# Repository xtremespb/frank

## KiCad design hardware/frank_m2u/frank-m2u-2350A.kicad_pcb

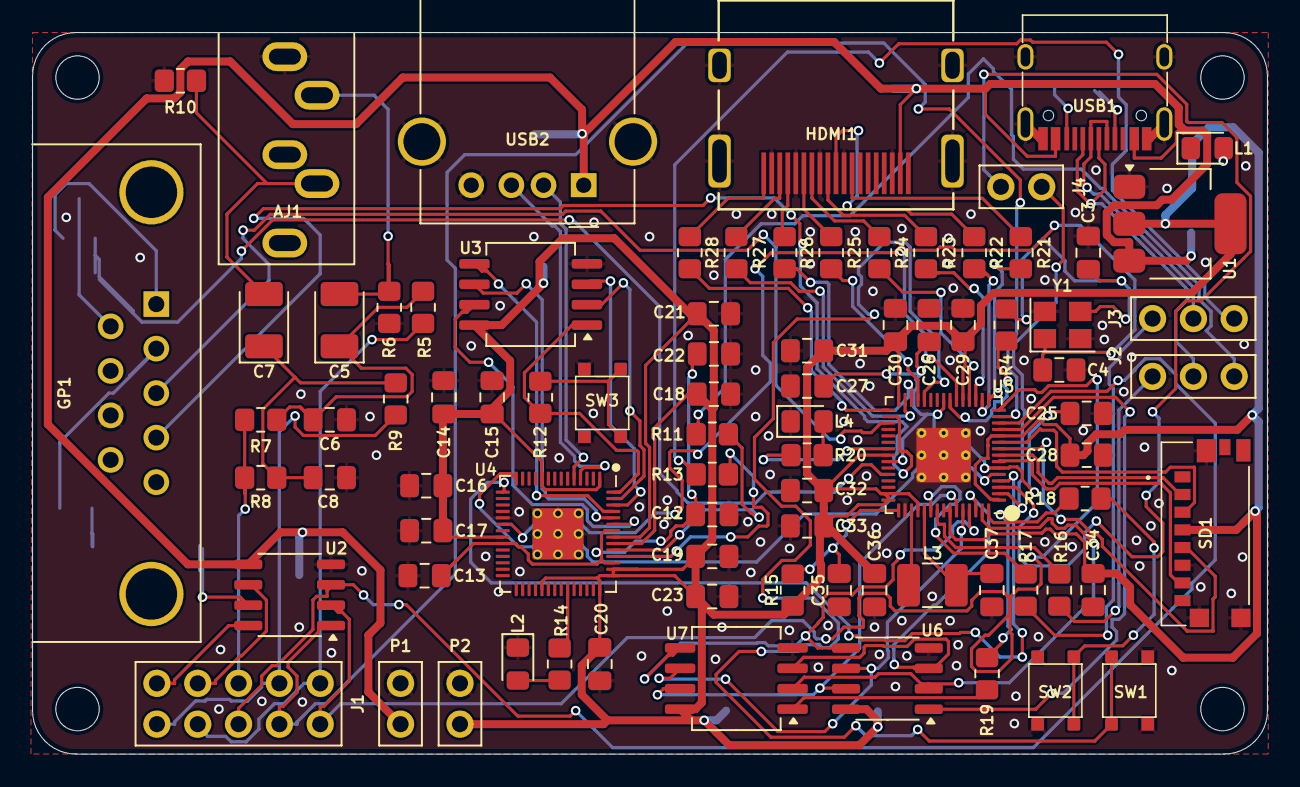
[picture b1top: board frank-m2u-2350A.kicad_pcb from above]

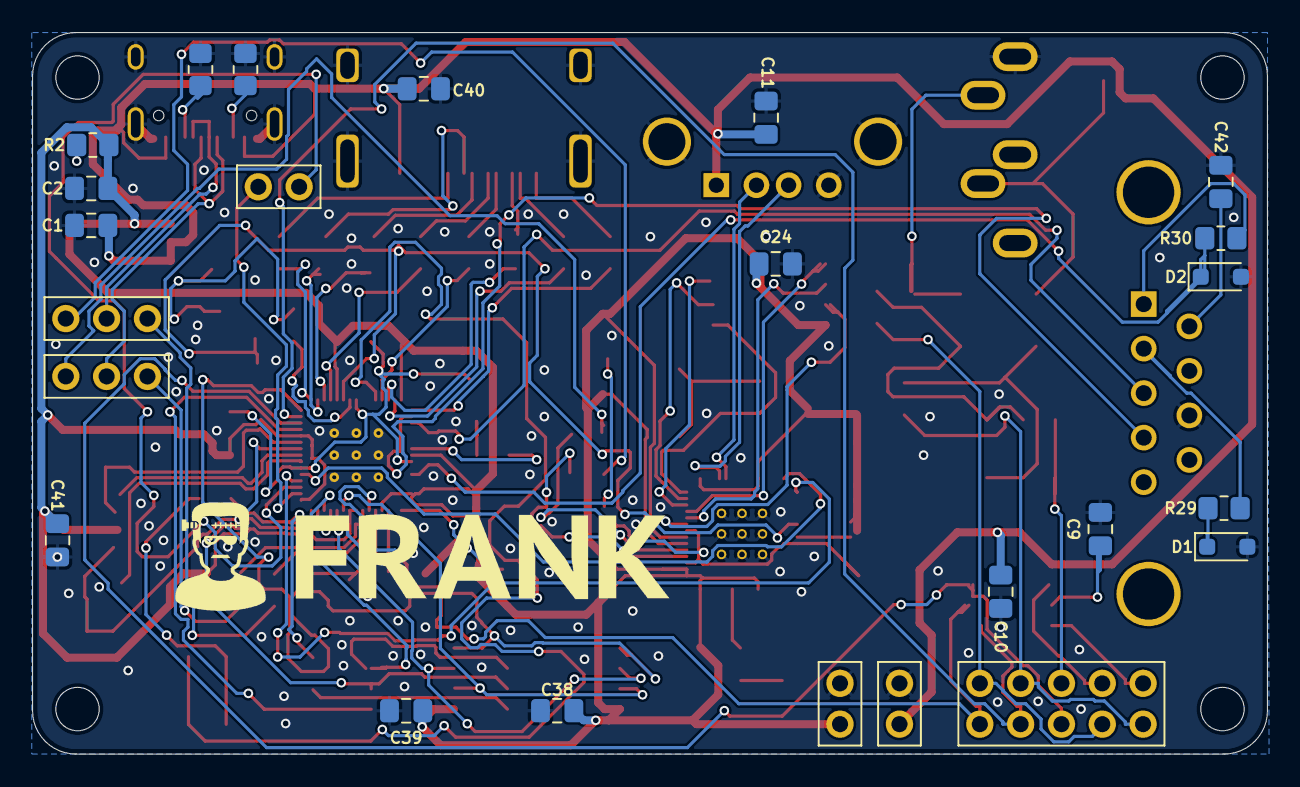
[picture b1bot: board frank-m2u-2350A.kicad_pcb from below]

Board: 2 copper layers, 76.8 x 44.9 mm, 105 parts (18 on the bottom side), 91 nets.

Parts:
AJ1: SJ1-353XNG; Jack (3.5mm)
C1, C2, C11: 10u; Capacitor (0805)
C3, C4: 15p; Capacitor (0805)
C5, C7: 10u; Capacitor (3528, tantalum, polar)
C6, C8: 10n; Capacitor (0805)
C9, C22, C23: 1u; Capacitor (0805)
C10: 47u; Capacitor (0805)
C12, C13, C14, C15, C16, C17, C18, C19, C20, C21, C24, C25, C27, C28, C29, C30, C31, C32, C33, C34, C38, C39, C40, C41, C42: 100n; Capacitor (0805)
C26, C35, C36, C37: 4.7u; Capacitor (0805)
D1, D2: 3V3; Diode (SOD-323)
GP1: Gamepad; D-SUB (9 pin, male, top mount)
H1, H2, H3, H4: MountingHole; Mounting Hole (2.7mm)
HDMI1: HDMI Female; HDMI (female)
J1: Pin Header 2x05; Pin Header (2x05)
J2: USB DP Jumper; Pin Header (1x03)
J3: USB DM Jumper; Pin Header (1x03)
J4: UART; Pin Header (1x02)
L1: Green; LED (0805)
L2: BLUE; LED (0805)
L3: 3.3uH; Inductor (3225)
L4: Blue; LED (0805)
P1: Power (+5V); Pin Header (1x02)
P2: Power (+3.3V); Pin Header (1x02)
R1, R3: 5.1K; Resistor (0805)
R2, R4, R5, R9, R12, R14, R18, R20, R29, R30: 1K; Resistor (0805)
R6, R10: 330R; Resistor (0805)
R7, R8: 2K; Resistor (0805)
R11, R13, R16, R17: 27R; Resistor (0805)
R15: 33R; Resistor (0805)
R19: 0R; Resistor (0805)
R21, R22, R23, R24, R25, R26, R27, R28: 270R; Resistor (0805)
SD1: 47571-0001; MicroSD (SMD, short)
SW1: Reset; Button (SMD, 3x3mm, 1-1)
SW2, SW3: Boot; Button (SMD, 3x3mm, 1-1)
U1: NCP1117 3.3; SOT-223
U2: TDA1387T; SO-8
U3: W25Q128JVSIQ; SOIC-8
U4: RP2040; QFN 56
U5: RP2350A; QFN 60 (RP2350A)
U6: ESP-PSRAM32; SO-8
U7: W25Q128JVSQ; SOIC-8
USB1: USB4215-03-A; USB Type C
USB2: 676430910; USB Type A (single)
Y1: 12 MHz; Crystal (3225)

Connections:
+3V3: C2.1, C14.1, C15.1, C16.1, C17.1, C18.1, C19.1, C20.1, C21.1, C23.1, C24.1, C28.1, C29.1, C30.1, C31.1, C32.1, C33.1, C34.1, C36.1, C38.1, C39.1, C41.2, P2.2, R2.2, R15.1, SD1.P4 (VDD), U1.2 (VO), U3.8 (VCC), U4.1 (IOVDD), U4.10 (IOVDD), U4.22 (IOVDD), U4.33 (IOVDD), U4.42 (IOVDD), U4.43 (ADC_AVDD), U4.44 (VREG_IN), U4.48 (USB_VDD), U4.49 (IOVDD), U5.1 (IOVDD), U5.11 (IOVDD), U5.20 (IOVDD), U5.30 (IOVDD), U5.38 (IOVDD), U5.44 (ADC_AVDD), U5.45 (IOVDD), U5.49 (VREG_VIN), U5.53 (USB_OTP_VDD), U5.54 (QSPI_IOVDD), U6.8 (VCC), U7.8 (VCC)
/A_OUTB: J1.5, R7.2, R8.2
/A_OUTL: J1.1, J1.8, R5.2
/A_OUTR: J1.3, J1.10, R9.2
/A_TDAL: J1.7, U2.6 (A_LEFT)
/A_TDAR: J1.9, U2.8 (A_RIGHT)
/Audio Out/L: AJ1.T, C5.2, R6.1
/Audio Out/R: AJ1.R, C7.2, R10.1
/GPIO0: J4.1, U5.2 (GPIO0)
/GPIO1: J4.2, U5.3 (GPIO1)
/GPIO2: U4.15 (GPIO12), U5.4 (GPIO2)
/GPIO3: U4.14 (GPIO11), U5.5 (GPIO3)
/GPIO4: SD1.P7 (DAT0), U5.7 (GPIO4)
/GPIO5: SD1.P2 (CD/DAT3), U5.8 (GPIO5)
/GPIO6: SD1.P5 (CLK), U5.9 (GPIO6)
/GPIO7: SD1.P3 (CMD), U5.10 (GPIO7)
/GPIO8: U5.12 (GPIO8), U6.1 (~CE)
/GPIO9: J1.6, U2.3 (DATA), U5.13 (GPIO9)
/GPIO10: J1.4, U2.1 (SCLK), U5.14 (GPIO10)
/GPIO11: J1.2, U2.2 (LRCK), U5.15 (GPIO11)
/GPIO12: R21.2, U5.16 (GPIO12)
/GPIO13: R22.2, U5.17 (GPIO13)
/GPIO14: R23.2, U5.18 (GPIO14)
/GPIO15: R24.2, U5.19 (GPIO15)
/GPIO16: R25.2, U5.27 (GPIO16)
/GPIO17: R26.2, U5.28 (GPIO17)
/GPIO18: R27.2, U5.29 (GPIO18)
/GPIO19: R28.2, U5.31 (GPIO19)
/GPIO20: GP1.4, U5.32 (GPIO20)
/GPIO21: GP1.3, U5.33 (GPIO21)
/GPIO26: D1.1 (K), R29.1
/GPIO27: D2.1 (K), R30.1, U5.41 (GPIO27_ADC1)
/Gamepad/+5V: C42.1, GP1.6
/Gamepad/J1_DATA: GP1.2, R29.2
/Gamepad/J2_DATA: GP1.1, R30.2
/P_DM: J3.2, USB1.5 (DN2), USB1.7 (DN1)
/P_DP: J2.2, USB1.6 (DP1), USB1.8 (DP2)
/RP1_DM: J3.1, R17.1
/RP1_DP: J2.1, R16.1
/RP2_DM: J3.3, R13.1
/RP2_DP: J2.3, R11.1
/RP2040/GPIO25: R14.2, U4.37 (GPIO25)
/RP2040/QSPI_SCLK: U3.6 (CLK), U4.52 (QSPI_SCLK)
/RP2040/QSPI_SD0: U3.5 (DI(IO0)), U4.53 (QSPI_SD0)
/RP2040/QSPI_SD1: U3.2 (DO(IO1)), U4.55 (QSPI_SD1)
/RP2040/QSPI_SD2: U3.3 (IO2), U4.54 (QSPI_SD2)
/RP2040/QSPI_SD3: U3.7 (IO3), U4.51 (QSPI_SD3)
/RP2040/QSPI_SS: R12.1, U3.1 (~CS), U4.56 (QSPI_SS)
/RP2040/~USB_BOOT: R12.2, SW3.2
/RP2350A/FLASH_SS: R19.2, U7.1 (~CS)
/RP2350A/QSPI_SCLK: U5.56 (QSPI_SCLK), U6.6 (SCLK), U7.6 (CLK)
/RP2350A/QSPI_SD0: U5.57 (QSPI_SD0), U6.5 (SI/SIO), U7.5 (DI(IO0))
/RP2350A/QSPI_SD1: U5.59 (QSPI_SD1), U6.2 (SO/SIO), U7.2 (DO(IO1))
/RP2350A/QSPI_SD2: U5.58 (QSPI_SD2), U6.3 (SIO2), U7.3 (IO2)
/RP2350A/QSPI_SD3: U5.55 (QSPI_SD3), U6.7 (SIO3), U7.7 (IO3)
/RP2350A/QSPI_SS: R18.1, R19.1, U5.60 (QSPI_SS)
/RP2350A/VREG_AVDD: C35.1, R15.2, U5.46 (VREG_AVDD)
/RP2350A/VREG_LX: L3.2, U5.48 (VREG_LX)
/RP2350A/~USB_BOOT: R18.2, SW2.2
/RUN: SW1.1, U5.26 (RUN)
/US_D1M: U4.5 (GPIO3), USB2.2 (D-)
/US_D1P: U4.4 (GPIO2), USB2.3 (D+)
/XIN: C4.1, U4.20 (XIN), U5.21 (XIN), Y1.1
/XOUT: R4.1, U5.22 (XOUT)
GND: AJ1.S, C1.2, C2.2, C3.2, C4.2, C6.2, C8.2, C9.2, C10.1, C11.1, C12.2, C13.2, C14.2, C15.2, C16.2, C17.2, C18.2, C19.2, C20.2, C21.2, C22.2, C23.2, C24.2, C25.2, C26.2, C27.2, C28.2, C29.2, C30.2, C31.2, C32.2, C33.2, C34.2, C35.2, C36.2, C37.2, C38.2, C39.2, C40.2, C41.1, C42.2, D1.2 (A), D2.2 (A), GP1.8, HDMI1.2 (G_D2), HDMI1.5 (G_D1), HDMI1.8 (G_D0), HDMI1.11 (G_CLK), HDMI1.17 (G_DDC/CEC), HDMI1.20 (SHIELD1), HDMI1.21 (SHIELD2), HDMI1.22 (SHIELD3), HDMI1.23 (SHIELD4), L1.1 (K), L2.1 (K), L4.1 (K), P1.1, P2.1, R1.1, R3.1, R6.2, R10.2, SD1.G1 (GND_1), SD1.G2 (GND_2), SD1.G3 (GND_3), SD1.P6 (VSS), SW1.2, SW2.1, SW3.1, U1.1 (GND), U2.4 (AGND), U3.4 (GND), U4.19 (TESTEN), U4.57 (GND), U5.47 (VREG_PGND), U5.61 (GND), U6.4 (VSS), U7.4 (GND), USB1.1 (GND), USB1.12 (GND), USB1.13 (SHIELD), USB2.4 (GND), USB2.5 (Shield), Y1.2, Y1.4
GPIO25: R20.2, U5.37 (GPIO25)
unnamed: C3.1, R4.2, Y1.3
unnamed: C5.1, C6.1, R5.1, R7.1
unnamed: C7.1, C8.1, R8.1, R9.1
unnamed: C25.1, C26.1, C27.1, U5.6 (DVDD), U5.23 (DVDD), U5.39 (DVDD)
unnamed: HDMI1.12 (CLKN), R21.1
unnamed: HDMI1.10 (CLKP), R22.1
unnamed: HDMI1.9 (D0N), R23.1
unnamed: HDMI1.7 (D0P), R24.1
unnamed: HDMI1.6 (D1N), R25.1
unnamed: HDMI1.4 (D1P), R26.1
unnamed: HDMI1.3 (D2N), R27.1
unnamed: HDMI1.1 (D2P), R28.1
unnamed: L1.2 (A), R2.1
unnamed: L2.2 (A), R14.1
unnamed: L4.2 (A), R20.1
unnamed: C9.1, U2.7 (FLT)
unnamed: R13.2, U4.46 (USB_DM)
unnamed: R11.2, U4.47 (USB_DP)
unnamed: C12.1, C13.1, C22.1, U4.23 (DVDD), U4.45 (VREG_VOUT), U4.50 (DVDD)
unnamed: R17.2, U5.51 (USB_DM)
unnamed: R16.2, U5.52 (USB_DP)
unnamed: C37.1, L3.1, U5.50 (VREG_FB)
unnamed: R1.2, USB1.4 (CC1)
unnamed: R3.2, USB1.10 (CC2)
VBUS: C1.1, C10.2, C11.2, C40.1, HDMI1.18 (+5V), P1.2, U1.3 (VI), U2.5 (VA), USB1.2 (VBUS), USB1.11 (VBUS), USB2.1 (VBUS)

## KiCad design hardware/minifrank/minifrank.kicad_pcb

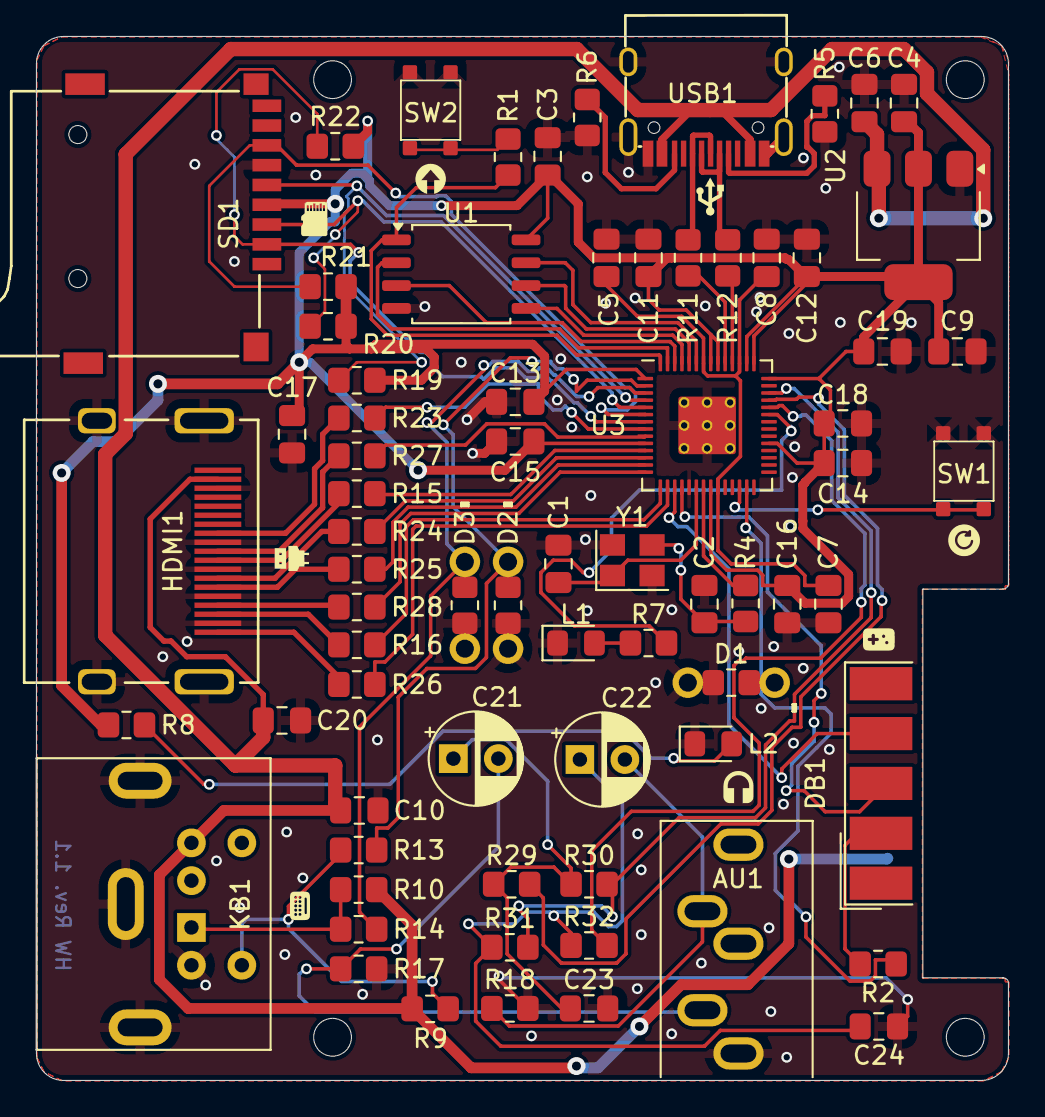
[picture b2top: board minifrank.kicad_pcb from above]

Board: 2 copper layers, 54.0 x 58.0 mm, 72 parts (0 on the bottom side), 59 nets.

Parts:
AU1: AUDIO OUT; Medved_Jack_3.5mm_CUI_SJ1-3535NG_Horizontal
C1, C2: 15p; C_0805_2012Metric_Pad1.18x1.45mm_HandSolder
C3, C5, C7, C11, C13, C14, C15, C16, C18, C19: 100n; C_0805_2012Metric_Pad1.18x1.45mm_HandSolder
C4, C6, C9: 10u; C_0805_2012Metric_Pad1.18x1.45mm_HandSolder
C8, C12: 1u; C_0805_2012Metric_Pad1.18x1.45mm_HandSolder
C10, C17, C20: 0.1u; C_0805_2012Metric_Pad1.18x1.45mm_HandSolder
C21, C22: 10u; Medved_CP_Radial_D5.0mm_P2.50mm
C23, C24: 10n; C_0805_2012Metric_Pad1.18x1.45mm_HandSolder
D1, D2, D3: 3V3; R_0805_PLUS
DB1: Joystick; DSUB-9_Male_EdgeMount_P2.77mm
HDMI1: HDMI
KB1: PS/2; Connector_Mini-DIN_Female_6Pin_2rows
L1, L2: LED; LED_0805_2012Metric_Pad1.15x1.40mm_HandSolder
R1, R2, R4, R9, R10, R29, R32: 1k; R_0805_2012Metric_Pad1.20x1.40mm_HandSolder
R5, R6: 5.1K; R_0805_2012Metric_Pad1.20x1.40mm_HandSolder
R7, R8: 1K; R_0805_2012Metric_Pad1.20x1.40mm_HandSolder
R11, R12: 27; R_0805_2012Metric_Pad1.20x1.40mm_HandSolder
R13, R14: 100R; R_0805_2012Metric_Pad1.20x1.40mm_HandSolder
R15, R16, R23, R24, R25, R26, R27, R28: 270R; R_0805_2012Metric_Pad1.20x1.40mm_HandSolder
R17, R18: 330R; R_0805_2012Metric_Pad1.20x1.40mm_HandSolder
R19, R20, R21, R22: 10K; R_0805_2012Metric_Pad1.20x1.40mm_HandSolder
R30, R31: 2k; R_0805_2012Metric_Pad1.20x1.40mm_HandSolder
SD1: Micro SD; Medved_SD_Card
SW1: Reset Button; Button_SMD_3x3x2
SW2: Flash Button; Button_SMD_3x3x2
U1: W25Q128JVS; SOIC-8_5.23x5.23mm_P1.27mm
U2: NCP1117-3.3_SOT223; Medved_SOT-223-3_TabPin2
U3: RP2040; RP2040-QFN-56
USB1: USB Type C; USB-TYPE-C-31-M-12_lib2
Y1: ABM8-272-T3; Crystal_SMD_3225-4Pin_3.2x2.5mm

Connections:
+1V1: C5.1, C7.1, C8.1, U3.23 (DVDD), U3.45 (VREG_VOUT), U3.50 (DVDD)
+3V3: C3.1, C4.1, C9.1, C11.1, C12.1, C13.1, C14.1, C15.1, C16.1, C17.2, C18.1, C19.1, R8.2, R19.2, R20.2, R21.2, R22.2, SD1.4 (VDD), U1.8 (VCC), U2.2 (VO), U3.1 (IOVDD), U3.10 (IOVDD), U3.22 (IOVDD), U3.33 (IOVDD), U3.42 (IOVDD), U3.43 (ADC_AVDD), U3.44 (VREG_IN), U3.48 (USB_VDD), U3.49 (IOVDD)
/CLKN: HDMI1.12 (CLKN), R23.1
/CLKP: HDMI1.10 (CLKP), R27.1
/D0N: HDMI1.9 (D0N), R15.1
/D0P: HDMI1.7 (D0P), R24.1
/D1N: HDMI1.6 (D1N), R25.1
/D1P: HDMI1.4 (D1P), R28.1
/D2N: HDMI1.3 (D2N), R16.1
/D2P: HDMI1.1 (D2P), R26.1
/D+: R11.1, USB1.6 (DP1), USB1.8 (DP2)
/D-: R12.1, USB1.5 (DN2), USB1.7 (DN1)
/GPIO0: D2.1 (K), R13.2, U3.2 (GPIO0)
/GPIO1: D3.1 (K), R14.2, U3.3 (GPIO1)
/GPIO2: R19.1, SD1.5 (CLK), U3.4 (GPIO2)
/GPIO3: R20.1, SD1.3 (CMD), U3.5 (GPIO3)
/GPIO4: R21.1, SD1.7 (DAT0), U3.6 (GPIO4)
/GPIO5: R22.1, SD1.2 (DAT3/CD), U3.7 (GPIO5)
/GPIO6: R23.2, U3.8 (GPIO6)
/GPIO7: R27.2, U3.9 (GPIO7)
/GPIO8: R15.2, U3.11 (GPIO8)
/GPIO9: R24.2, U3.12 (GPIO9)
/GPIO10: R25.2, U3.13 (GPIO10)
/GPIO11: R28.2, U3.14 (GPIO11)
/GPIO12: R16.2, U3.15 (GPIO12)
/GPIO13: R26.2, U3.16 (GPIO13)
/GPIO14: DB1.4, U3.17 (GPIO14)
/GPIO15: DB1.3, U3.18 (GPIO15)
/GPIO16: D1.1 (K), R2.1, U3.27 (GPIO16)
/GPIO25: R7.2, U3.37 (GPIO25)
/GPIO26: R32.2, U3.38 (GPIO26_ADC0)
/GPIO27: R29.2, U3.39 (GPIO27_ADC1)
/GPIO28: R30.2, R31.2, U3.40 (GPIO28_ADC2)
/J1_DATA: DB1.2, R2.2
/L: AU1.T, C21.2, R17.1
/PS/2 CLK: KB1.5, R9.2, R13.1
/PS/2 DATA: KB1.1, R10.2, R14.1
/QSPI_SCLK: U1.6 (CLK), U3.52 (QSPI_SCLK)
/QSPI_SD0: U1.5 (DI(IO0)), U3.53 (QSPI_SD0)
/QSPI_SD1: U1.2 (DO(IO1)), U3.55 (QSPI_SD1)
/QSPI_SD2: U1.3 (IO2), U3.54 (QSPI_SD2)
/QSPI_SD3: U1.7 (IO3), U3.51 (QSPI_SD3)
/QSPI_SS: R1.1, U1.1 (~CS), U3.56 (QSPI_SS)
/R: AU1.R, C22.2, R18.1
/RUN: SW1.2, SW1.4, U3.26 (RUN)
/XIN: C1.1, U3.20 (XIN), Y1.1
/XOUT: R4.1, U3.21 (XOUT)
/~USB_BOOT: R1.2, SW2.2, SW2.4
GND: AU1.S, C1.2, C2.2, C3.2, C4.2, C5.2, C6.2, C7.2, C8.2, C9.2, C10.2, C11.2, C12.2, C13.2, C14.2, C15.2, C16.2, C17.1, C18.2, C19.2, C20.2, C23.2, C24.2, D1.2 (A), D2.2 (A), D3.2 (A), DB1.8, HDMI1.2 (G_D2), HDMI1.5 (G_D1), HDMI1.8 (G_D0), HDMI1.11 (G_CLK), HDMI1.17 (G_DDC/CEC), HDMI1.20 (SHIELD1), HDMI1.21 (SHIELD2), HDMI1.22 (SHIELD3), HDMI1.23 (SHIELD4), KB1.3, L1.1 (K), L2.1 (K), R5.1, R6.1, R17.2, R18.2, SD1.6 (VSS), SW1.1, SW1.3, SW2.1, SW2.3, U1.4 (GND), U2.1 (GND), U3.19 (TESTEN), U3.57 (GND), USB1.1 (GND), USB1.12 (GND), USB1.13 (SHIELD), Y1.2, Y1.4
unnamed: C2.1, R4.2, Y1.3
unnamed: C21.1, C23.1, R29.1, R30.1
unnamed: C22.1, C24.1, R31.1, R32.1
unnamed: L1.2 (A), R7.1
unnamed: L2.2 (A), R8.1
unnamed: R12.2, U3.46 (USB_DM)
unnamed: R11.2, U3.47 (USB_DP)
unnamed: R5.2, USB1.4 (CC1)
unnamed: R6.2, USB1.10 (CC2)
VBUS: C6.1, C10.1, C20.1, DB1.6, HDMI1.18 (+5V), KB1.4, R9.1, R10.1, U2.3 (VI), USB1.2 (VBUS), USB1.11 (VBUS)

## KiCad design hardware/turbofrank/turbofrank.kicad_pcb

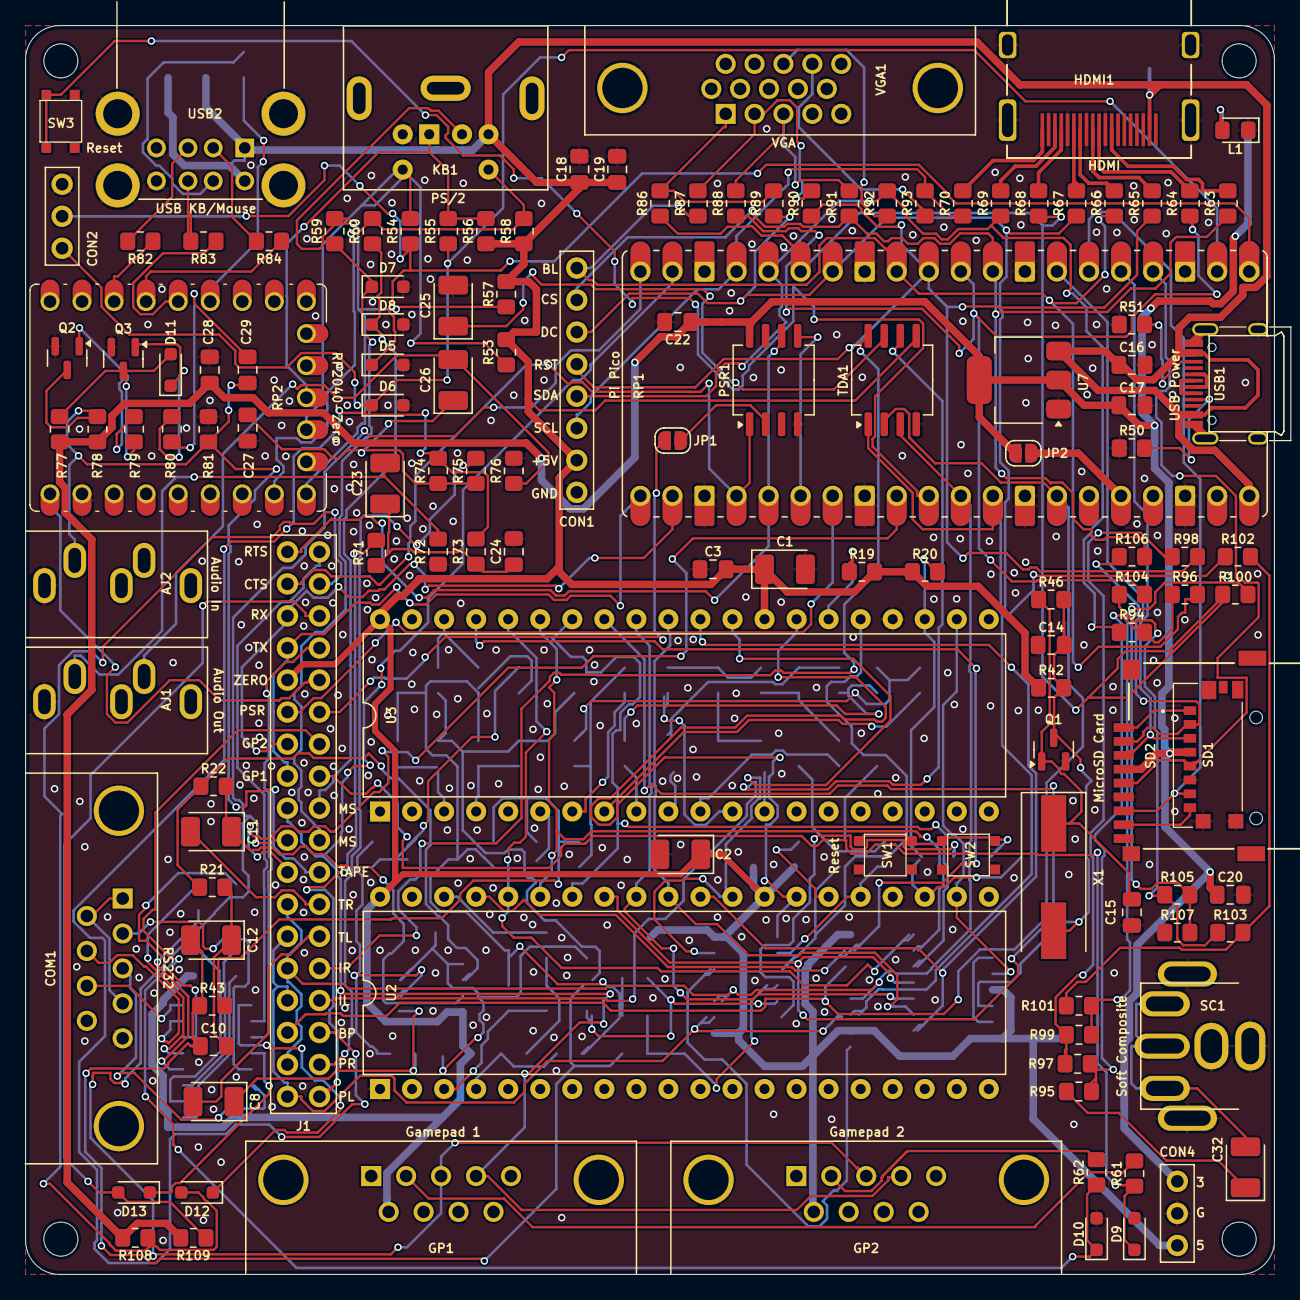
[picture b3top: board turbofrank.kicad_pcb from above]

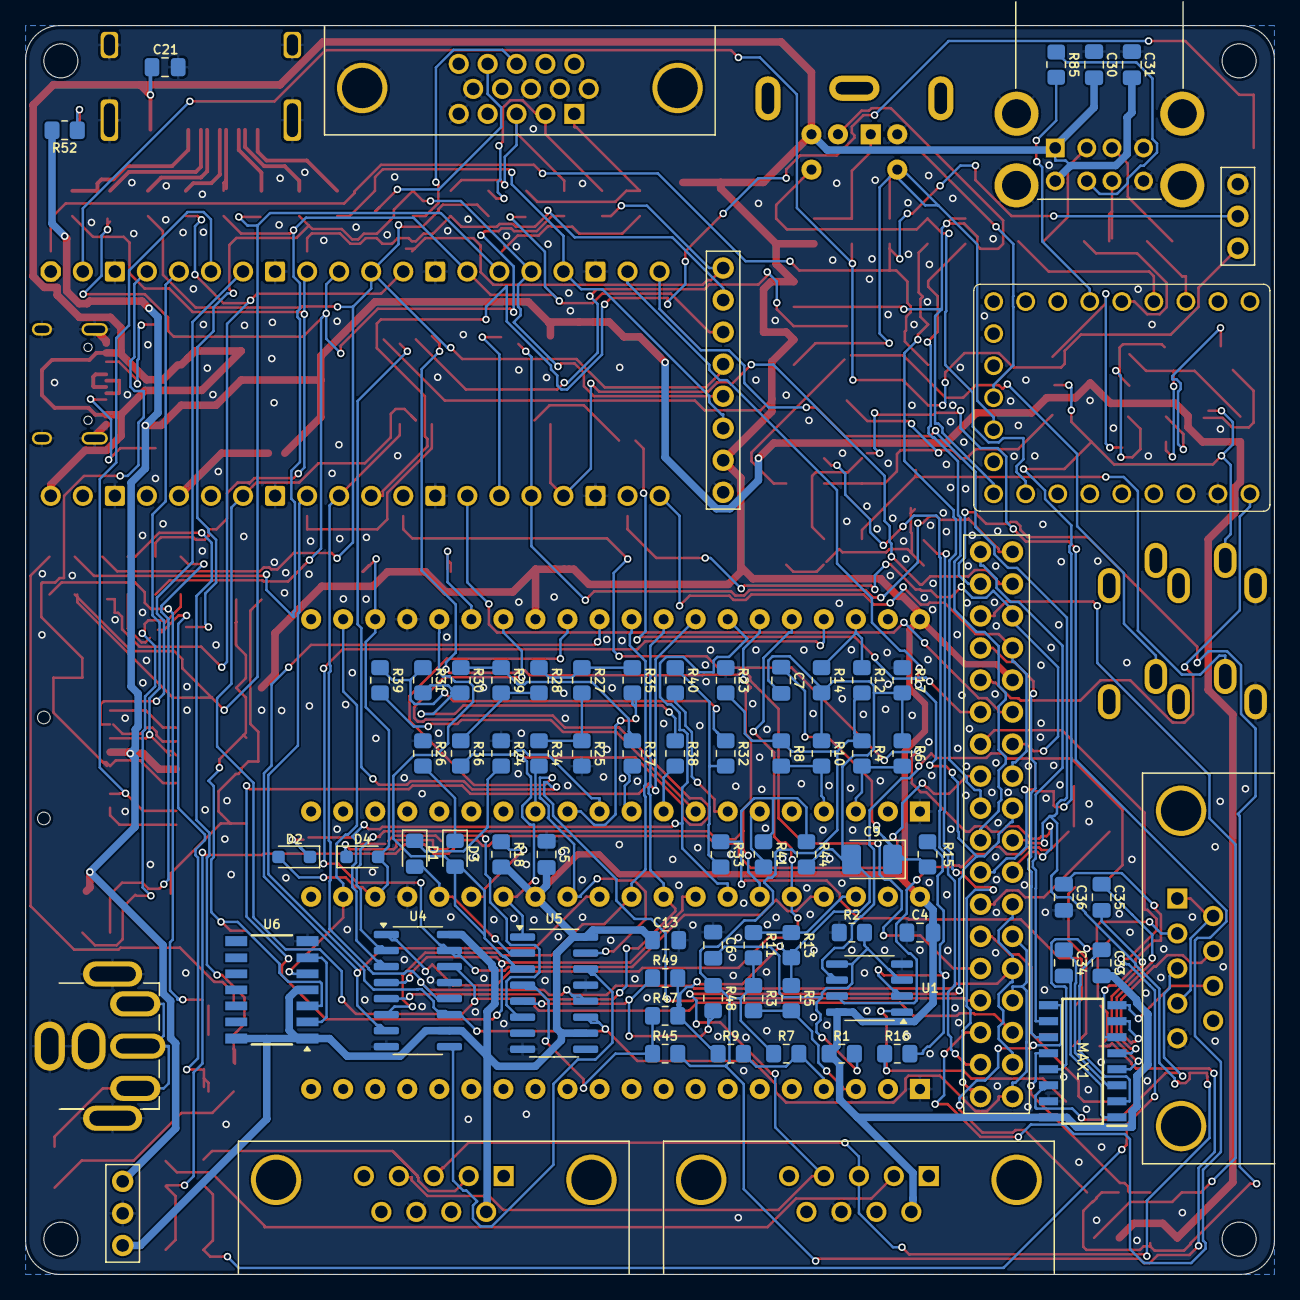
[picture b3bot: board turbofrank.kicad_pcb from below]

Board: 2 copper layers, 99.0 x 99.0 mm, 201 parts (66 on the bottom side), 171 nets.

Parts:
AJ1: Audio Out; Jack (3.5mm)
AJ2: Audio In; Jack (3.5mm)
C1, C2: 100u; Capacitor (3528, tantalum, polar)
C3, C5, C7, C10, C18, C19, C20, C21, C22, C28, C29: 100n; Capacitor (0805)
C4, C6, C16, C17, C30, C31: 10u; Capacitor (0805)
C8, C9, C11, C12: 10u; Capacitor (3528, tantalum, polar)
C13: 0.1; Capacitor (0805)
C14, C15: 22p; Capacitor (0805)
C23, C25, C26: 10u*; Capacitor (3528, tantalum, polar)
C24, C27: 10n; Capacitor (0805)
C32: 220u; Capacitor (3528, tantalum, polar)
C33, C34, C35, C36: 1u; Capacitor (0805)
COM1: RS232; D-SUB (9 pin, male, top mount)
CON1: Display; Pin Header (1x08)
CON2: UART; Pin Header (1x03)
CON4: Power; Pin Header (1x03)
D1, D3: LED; LED (0805)
D2, D4: 1N4148W; Diode (SOD-323)
D5, D6, D7, D8, D9, D10: 3V3; Diode (SOD-323)
D11, D12, D13: 1N4148; Diode (SOD-323)
GP1, GP2: Gamepad; D-SUB (9 pin, male, top mount)
H1, H2, H3, H4: MountingHole; Mounting Hole (2.7mm)
HDMI1: HDMI Female; HDMI (female)
J1: Main Jumper Set; Pin Header (2x18)
JP1, JP2: Jumper PSRAM (2.54); Jumper (solder)
KB1: PS/2; MiniDIN (6 Pin, female)
L1: GREEN; LED (0805)
MAX1: MAX232CSE+; SOIC127P600X175-16N
PSR1: ESP-PSRAM32; SOIC-8
Q1, Q2, Q3: BC850; SOT-23
R1, R2, R46: 100K; Resistor (0805)
R3, R4, R5, R6, R7, R8, R9, R10, R11, R12, R13, R14, R73, R74: 2K; Resistor (0805)
R15, R20, R21, R43, R44, R45, R47, R48, R49, R77, R79, R80: 10K; Resistor (0805)
R16, R22: 47K; Resistor (0805)
R17, R23: 120R; Resistor (0805)
R18, R19, R24, R26, R42, R52, R53, R57, R58, R61, R62, R71, R75, R78, R108, R109: 1K; Resistor (0805)
R25, R34, R35, R36, R37, R38, R39, R40, R41: 2R; Resistor (0805)
R27, R28, R29, R30, R31, R32, R33: 1R; Resistor (0805)
R50, R51: 5.1K; Resistor (0805)
R54, R55, R59, R60, R81, R92, R93: 100R; Resistor (0805)
R56, R89, R90, R91: 1k; Resistor (0805)
R63, R64, R65, R66, R67, R68, R69, R70, R96, R98, R100, R102, R104, R106: 270R; Resistor (0805)
R72, R76, R86, R87, R88: 330R; Resistor (0805)
R82, R83, R84, R85: 22R; Resistor (0805)
R94: 750R; Resistor (0805)
R95: 51R*; Resistor (0805)
R97, R99, R101, R103, R105: 150R; Resistor (0805)
R107: 300R; Resistor (0805)
RP1: RP Pico; Raspberry Pi Pico
RP2: RP 2040 Zero; Raspberry Pi Zero
SC1: VIDEO (Soft Composite); RCA
SD1: Micro SD (Short); MicroSD (SMD, short)
SD2: Micro SD (Long); MicroSD (SMD, long)
SW1, SW2: SW_Push; Button (SMD, 3x3mm, 1-1)
SW3: Reset Button; Button (SMD, 3x3mm)
TDA1: TDA1387T; SOIC-8
U1: LM358; SO-8
U2, U3: YM2149; DIP-40
U4, U5: 74HC595; SOP-16
U6: 74HC74; 74HCT74D
U7: NCP1117 3.3; SOT-223
USB1: USB Type C
USB2: USB_A_Stacked; USB Type A (stacked)
VGA1: VGA; D-SUB (15 pin, female)
X1: 3.58 MHz; Crystal (HC49-S)

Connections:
+3V3: C17.1, C20.2, C22.1, C28.1, CON4.1, JP2.2 (B), PSR1.8 (VCC), R52.2, R77.1, R78.1, R108.2, R109.2, SD1.P4 (VDD), SD2.4 (VDD), U7.2 (VO)
/A_OUTB: J1.5, R73.2, R74.2
/A_OUTL: J1.1, R71.2
/A_OUTR: J1.3, R75.2
/A_TDAL: J1.7, TDA1.6 (A_LEFT)
/A_TDAR: J1.9, TDA1.8 (A_RIGHT)
/A_TSL: C8.2, J1.11
/A_TSR: C11.2, J1.13
/Audio Out/L: AJ1.T, C23.2, R72.1
/Audio Out/R: AJ1.R, C26.2, R76.1
/Audio Out/TurboSound/A1: R7.2, R9.2, U2.4 (B)
/Audio Out/TurboSound/A2: R8.2, R10.2, U3.4 (B)
/Audio Out/TurboSound/B1: R3.2, R5.2, U2.3 (A)
/Audio Out/TurboSound/B2: R4.2, R6.2, U3.3 (A)
/Audio Out/TurboSound/BEEP: R45.2, R47.2, U5.4 (QE)
/Audio Out/TurboSound/C1: R11.2, R13.2, U2.38 (C)
/Audio Out/TurboSound/C2: R12.2, R14.2, U3.38 (C)
/Audio Out/TurboSound/CLK_1.75M: U2.22 (CLOCK), U3.22 (CLOCK), U6.5 (Q)
/Audio Out/TurboSound/COVOX_OUT: R33.2, R41.1, R43.2, R44.2
/Audio Out/TurboSound/DA0: U2.37 (DA0), U3.37 (DA0), U4.15 (QA)
/Audio Out/TurboSound/DA1: U2.36 (DA1), U3.36 (DA1), U4.1 (QB)
/Audio Out/TurboSound/DA2: U2.35 (DA2), U3.35 (DA2), U4.2 (QC)
/Audio Out/TurboSound/DA3: U2.34 (DA3), U3.34 (DA3), U4.3 (QD)
/Audio Out/TurboSound/DA4: U2.33 (DA4), U3.33 (DA4), U4.4 (QE)
/Audio Out/TurboSound/DA5: U2.32 (DA5), U3.32 (DA5), U4.5 (QF)
/Audio Out/TurboSound/DA6: U2.31 (DA6), U3.31 (DA6), U4.6 (QG)
/Audio Out/TurboSound/DA7: U2.30 (DA7), U3.30 (DA7), U4.7 (QH)
/Audio Out/TurboSound/DAC0: R34.2, U3.13 (IOB0)
/Audio Out/TurboSound/DAC1: R35.2, U3.12 (IOB1)
/Audio Out/TurboSound/DAC2: R36.2, U3.11 (IOB2)
/Audio Out/TurboSound/DAC3: R37.2, U3.10 (IOB3)
/Audio Out/TurboSound/DAC4: R38.2, U3.9 (IOB4)
/Audio Out/TurboSound/DAC5: R39.2, U3.8 (IOB5)
/Audio Out/TurboSound/DAC6: R40.2, U3.7 (IOB6)
/Audio Out/TurboSound/DAC7: R41.2, U3.6 (IOB7)
/Audio Out/TurboSound/L_IN: C7.1, C9.2, R5.1, R6.1, R9.1, R10.1, R13.1, R14.1, R17.1, R44.1, R47.1, R49.1
/Audio Out/TurboSound/R_IN: C10.1, C12.2, R3.1, R4.1, R7.1, R8.1, R11.1, R12.1, R23.1, R43.1, R45.1, R48.1
/Audio Out/TurboSound/SAVE: R48.2, R49.2, U5.5 (QF)
/Audio Out/TurboSound/YM_BC1: U2.29 (BC1), U3.29 (BC1), U5.15 (QA)
/Audio Out/TurboSound/YM_BDIR: U2.27 (BDIR), U3.27 (BDIR), U5.1 (QB)
/Audio Out/TurboSound/YM_CS1: D1.2 (A), U2.25 (A8), U5.2 (QC)
/Audio Out/TurboSound/YM_CS2: D3.2 (A), U3.25 (A8), U5.3 (QD)
/Audio Out/TurboSound/YM_RST: D2.2 (A), D4.2 (A), R20.1, U2.23 (~RESET), U3.23 (~RESET)
/Audio Out/TurboSound/YM_SEL1: R18.2, U2.26 (~SEL)
/Audio Out/TurboSound/YM_SEL2: R19.2, U3.26 (~SEL)
/Composite/CVBS: C32.2, SC1.1
/GP1_DATA: D9.1 (K), J1.21, R61.1
/GP2_DATA: D10.1 (K), J1.23, R62.1
/GPIO0: CON2.2, D5.1 (K), R54.2, RP1.1 (GPIO0)
/GPIO1: CON2.3, D6.1 (K), R55.2, RP1.2 (GPIO1)
/GPIO2: RP1.4 (GPIO2), SD1.P5 (CLK), SD2.5 (CLK)
/GPIO3: RP1.5 (GPIO3), SD1.P3 (CMD), SD2.3 (CMD)
/GPIO4: RP1.6 (GPIO4), SD1.P7 (DAT0), SD2.7 (DAT0)
/GPIO5: RP1.7 (GPIO5), SD1.P2 (CD/DAT3), SD2.2 (DAT3/CD)
/GPIO6: CON1.7, R63.2, R91.1, R106.1, RP1.9 (GPIO6)
/GPIO7: R64.2, R88.1, R104.1, RP1.10 (GPIO7)
/GPIO8: CON1.5, R65.2, R90.1, R98.1, RP1.11 (GPIO8)
/GPIO9: CON1.8, R66.2, R87.1, R96.1, RP1.12 (GPIO9)
/GPIO10: CON1.6, R67.2, R89.1, R102.1, RP1.14 (GPIO10)
/GPIO11: R68.2, R86.1, R100.1, RP1.15 (GPIO11)
/GPIO12: CON1.4, R69.2, R92.2, R94.1, RP1.16 (GPIO12)
/GPIO13: CON1.3, R70.2, R93.2, RP1.17 (GPIO13)
/GPIO14: GP1.4, GP2.4, J1.20, RP1.19 (GPIO14)
/GPIO15: GP1.3, GP2.3, J1.18, RP1.20 (GPIO15)
/GPIO16: J1.22, J1.30, RP1.21 (GPIO16)
/GPIO17: J1.24, J1.32, RP1.22 (GPIO17)
/GPIO18: J1.34, PSR1.1 (~CE), RP1.24 (GPIO18)
/GPIO19: J1.36, PSR1.6 (SCLK), RP1.25 (GPIO19)
/GPIO20: PSR1.5 (SI/SIO), RP1.26 (GPIO20)
/GPIO21: J1.26, RP1.27 (GPIO21)
/GPIO22: J1.16, RP1.29 (GPIO22)
/GPIO26: J1.4, J1.10, J1.14, RP1.31 (GPIO26_ADC0), TDA1.3 (DATA), U4.12 (RCLK), U5.12 (RCLK)
/GPIO27: J1.2, J1.8, J1.12, RP1.32 (GPIO27_ADC1), TDA1.1 (SCLK), U4.11 (SRCLK), U5.11 (SRCLK)
/GPIO28: J1.6, RP1.34 (GPIO28_ADC2), TDA1.2 (LRCK), U4.14 (SER)
/KB_CLK: KB1.5, R53.2, R54.1, RP2.13 (12)
/KB_DATA: KB1.1, R55.1, R56.2, RP2.12 (11)
/LOAD_IN_D: AJ2.T, C29.1, J1.15, Q2.3 (C), R78.2, R81.1
/MS_CLK: KB1.6, R58.2, R60.1, RP2.16 (15)
/MS_CLK_3V: D8.1 (K), J1.19, R60.2
/MS_DATA: KB1.2, R57.2, R59.1, RP2.15 (14)
/MS_DATA_3V: D7.1 (K), J1.17, R59.2
/Micro SD/DAT1: SD1.P8 (DAT1), SD2.8 (DAT1)
/Micro SD/DAT2: SD1.P1 (DAT2), SD2.1 (DAT2)
/PSR_SOSIO: J1.25, JP1.2 (B)
/Power/D+: USB1.6 (DP1), USB1.8 (DP2)
/Power/D-: USB1.5 (DN2), USB1.7 (DN1)
/RS232/C1+: C34.2, MAX1.1 (C1+)
/RS232/C1-: C34.1, MAX1.3 (C1-)
/RS232/C2+: C35.2, MAX1.4 (C2+)
/RS232/C2-: C35.1, MAX1.5 (C2-)
/RS232/CTS_IN: COM1.7, MAX1.7 (T2OUT)
/RS232/CTS_MAX: D12.1 (K), MAX1.9 (R2OUT)
/RS232/RTS_IN: COM1.8, MAX1.8 (R2IN)
/RS232/RX_IN: COM1.3, MAX1.14 (T1OUT)
/RS232/RX_MAX: D13.1 (K), MAX1.12 (R1OUT)
/RS232/TX_IN: COM1.2, MAX1.13 (R1IN)
/RS232/V+: C33.1, MAX1.2 (V+)
/RS232/V-: C36.1, MAX1.6 (V-)
/RS232_CTS: D12.2 (A), J1.33, R108.1
/RS232_RTS: J1.35, MAX1.10 (T2IN)
/RS232_RX: D13.2 (A), J1.31, R109.1
/RS232_TX: J1.29, MAX1.11 (T1IN)
/RUN: RP1.30 (RUN), SW3.3, SW3.4
/USB_D1M: R84.1, RP2.4 (3)
/USB_D1P: R82.1, RP2.3 (2)
/USB_D2M: R85.1, RP2.6 (5)
/USB_D2P: R83.1, RP2.5 (4)
/ZERO_VBUS: J1.27, RP2.23 (5V)
GND: AJ1.S, AJ2.S, C1.2, C2.2, C3.2, C4.2, C5.2, C6.2, C13.2, C14.1, C15.1, C16.2, C17.2, C18.2, C19.2, C20.1, C21.2, C22.2, C24.2, C25.2, C27.2, C28.2, C30.2, C31.2, C36.2, COM1.5, CON1.1, CON2.1, CON4.2, D5.2 (A), D6.2 (A), D7.2 (A), D8.2 (A), D9.2 (A), D10.2 (A), GP1.8, GP2.8, HDMI1.2 (G_D2), HDMI1.5 (G_D1), HDMI1.8 (G_D0), HDMI1.11 (G_CLK), HDMI1.17 (G_DDC/CEC), HDMI1.20 (SHIELD1), HDMI1.21 (SHIELD2), HDMI1.22 (SHIELD3), HDMI1.23 (SHIELD4), KB1.3, L1.1 (K), MAX1.15 (GND), PSR1.4 (VSS), Q1.2 (E), Q2.2 (E), Q3.2 (E), R2.2, R17.2, R23.2, R24.1, R25.1, R26.1, R50.1, R51.1, R72.2, R76.2, R81.2, R107.1, RP1.3 (GND), RP1.8 (GND), RP1.13 (GND), RP1.18 (GND), RP1.23 (GND), RP1.28 (GND), RP1.33 (AGND), RP1.38 (GND), RP2.22 (GND), SC1.2, SD1.G1 (GND_1), SD1.G2 (GND_2), SD1.G3 (GND_3), SD1.P6 (VSS), SD2.6 (VSS), SW1.2, SW2.2, SW3.1, SW3.2, TDA1.4 (AGND), U1.4 (V-), U2.1 (VSS), U2.24 (~A9), U3.1 (VSS), U3.24 (~A9), U4.8 (GND), U4.13 (~OE), U5.8 (GND), U5.13 (~OE), U6.7 (GND), U7.1 (GND), USB1.1 (GND), USB1.12 (GND), USB1.13 (SHIELD), USB2.4 (GND1), USB2.8 (GND2), USB2.9 (Shield), VGA1.0, VGA1.5, VGA1.6, VGA1.7, VGA1.8, VGA1.10
unnamed: C7.2, C9.1, R15.2
unnamed: C8.1, R16.1, U1.1
unnamed: C10.2, C12.1, R21.2
unnamed: C11.1, R22.1, U1.7
unnamed: C23.1, C24.1, R71.1, R73.1
unnamed: C26.1, C27.1, R74.1, R75.1
unnamed: C29.2, R80.1
unnamed: C32.1, R95.2
unnamed: COM1.1, COM1.4, COM1.6
unnamed: D1.1 (K), R24.2
unnamed: D2.1 (K), SW1.1, SW2.1
unnamed: D3.1 (K), R26.2
unnamed: D4.1 (K), U5.6 (QG)
unnamed: D11.2 (A), Q3.3 (C), R77.2, R79.1
unnamed: D11.1 (K), Q3.1 (B), R80.2
unnamed: GP1.2, R61.2
unnamed: GP2.2, R62.2
unnamed: HDMI1.12 (CLKN), R63.1
unnamed: HDMI1.10 (CLKP), R64.1
unnamed: HDMI1.9 (D0N), R65.1
unnamed: HDMI1.7 (D0P), R66.1
unnamed: HDMI1.6 (D1N), R67.1
unnamed: HDMI1.4 (D1P), R68.1
unnamed: HDMI1.3 (D2N), R69.1
unnamed: HDMI1.1 (D2P), R70.1
unnamed: JP1.1 (A), PSR1.2 (SO/SIO)
unnamed: JP2.1 (A), RP1.36 (3V3)
unnamed: L1.2 (A), R52.1
unnamed: C15.2, Q1.1 (B), R46.1, X1.1
unnamed: C14.2, Q1.3 (C), R42.1, R46.2, U6.3 (C), X1.2
unnamed: Q2.1 (B), R79.2
unnamed: R25.2, R27.1, R34.1
unnamed: R27.2, R28.1, R35.1
unnamed: R28.2, R29.1, R36.1
unnamed: R29.2, R30.1, R37.1
unnamed: R30.2, R31.1, R38.1
unnamed: R31.2, R32.1, R39.1
unnamed: R32.2, R33.1, R40.1
unnamed: R86.2, R89.2, VGA1.1
unnamed: R87.2, R90.2, VGA1.2
unnamed: R88.2, R91.2, VGA1.3
unnamed: R92.1, VGA1.13
unnamed: R93.1, VGA1.14
unnamed: R94.2, R95.1, R96.2, R97.2
unnamed: R97.1, R98.2, R99.2
unnamed: R99.1, R100.2, R101.2
unnamed: R101.1, R102.2, R103.2
unnamed: R103.1, R104.2, R105.2
unnamed: R105.1, R106.2, R107.2
unnamed: C25.1, TDA1.7 (FLT)
unnamed: C6.1, R1.2, R2.1, U1.3 (+), U1.5 (+)
unnamed: R15.1, R16.2, U1.2 (-)
unnamed: R21.1, R22.2, U1.6 (-)
unnamed: U4.9 (QH'), U5.14 (SER)
unnamed: U6.2 (D), U6.6 (~Q)
unnamed: R50.2, USB1.4 (CC1)
unnamed: R51.2, USB1.10 (CC2)
unnamed: R82.2, USB2.3 (D1+)
unnamed: R84.2, USB2.2 (D1-)
unnamed: R83.2, USB2.7 (D2+)
unnamed: R85.2, USB2.6 (D2-)
VBUS: C1.1, C2.1, C3.1, C4.1, C5.1, C13.1, C16.1, C18.1, C19.1, C21.1, C30.1, C31.1, C33.2, CON1.2, CON4.3, GP1.6, GP2.6, HDMI1.18 (+5V), J1.28, KB1.4, MAX1.16 (VCC), R1.1, R18.1, R19.1, R20.2, R42.2, R53.1, R56.1, R57.1, R58.1, RP1.40 (VBUS), TDA1.5 (VA), U1.8 (V+), U2.28 (BC2), U2.40 (VCC), U3.28 (BC2), U3.40 (VCC), U4.10 (~SRCLR), U4.16 (VCC), U5.10 (~SRCLR), U5.16 (VCC), U6.1 (~R), U6.4 (~S), U6.14 (VCC), U7.3 (VI), USB1.2 (VBUS), USB1.11 (VBUS), USB2.1 (VBUS1), USB2.5 (VBUS2)

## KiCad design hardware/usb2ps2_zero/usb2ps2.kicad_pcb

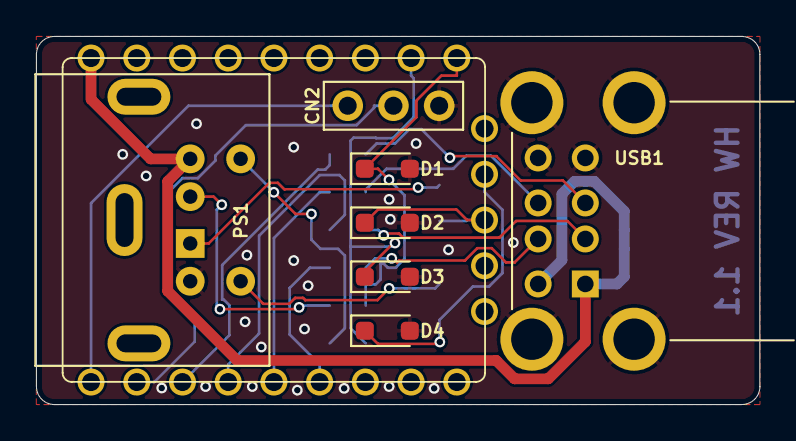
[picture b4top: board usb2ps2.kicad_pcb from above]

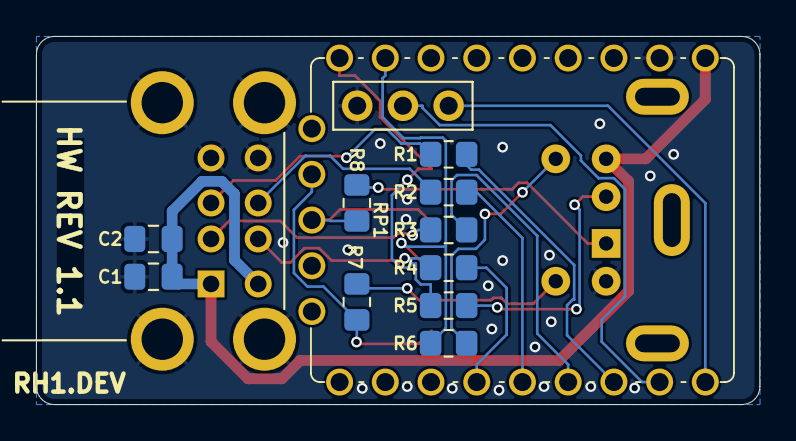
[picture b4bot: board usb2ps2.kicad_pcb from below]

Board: 2 copper layers, 40.2 x 20.4 mm, 18 parts (11 on the bottom side), 20 nets.

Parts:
C1, C2: 10u; Capacitor (0805)
CN2: UART; Pin Header (1x03)
D1, D2, D3, D4: 3V3; Diode (SOD-323)
PS1: PS/2; MiniDIN (6 Pin, female)
R1, R2, R3, R4: 22R; Resistor (0805)
R5, R6, R7, R8: 100R; Resistor (0805)
RP1: RP 2040 Zero; Raspberry Pi Zero (Outer pins)
USB1: USB_A_Stacked; USB Type A (stacked)

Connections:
/GPIO0: CN2.1, RP1.1 (0)
/GPIO1: CN2.2, RP1.2 (1)
/GPIO2: R1.1, RP1.3 (2)
/GPIO3: R3.1, RP1.4 (3)
/GPIO4: R2.1, RP1.5 (4)
/GPIO5: R4.1, RP1.6 (5)
/GPIO11: D2.1 (K), R8.2, RP1.12 (11)
/GPIO12: D4.1 (K), R7.2, RP1.13 (12)
/GPIO14: D1.1 (K), R5.2, RP1.15 (14)
/GPIO15: D3.1 (K), R6.2, RP1.16 (15)
/PS2 with Diodes/KB_CLK: PS1.5, R7.1
/PS2 with Diodes/KB_DATA: PS1.1, R8.1
/PS2 with Diodes/MS_CLK: PS1.6, R6.1
/PS2 with Diodes/MS_DATA: PS1.2, R5.1
GND: C1.2, C2.2, CN2.3, D1.2 (A), D2.2 (A), D3.2 (A), D4.2 (A), PS1.3, RP1.22 (GND), USB1.4 (GND1), USB1.8 (GND2), USB1.9 (Shield)
unnamed: R1.2, USB1.3 (D1+)
unnamed: R3.2, USB1.2 (D1-)
unnamed: R2.2, USB1.7 (D2+)
unnamed: R4.2, USB1.6 (D2-)
VBUS: C1.1, C2.1, PS1.4, RP1.23 (5V), USB1.1 (VBUS1), USB1.5 (VBUS2)

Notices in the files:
hardware/minifrank/minifrank.kicad_pcb:
© 2024 Mikhail Matveev
